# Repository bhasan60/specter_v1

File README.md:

## The Story Behind Specter V1
Welcome to the Specter V1! This is a custom 9-key macropad that I designed from the ground up. I wanted a dedicated board just for fun and maybe some custom shortcuts, but more importantly, I wanted to challenge myself to handle every single step of the hardware and software design process.

While I have a lot of experience with 3D modeling in Onshape, designing a custom 2-layer PCB from scratch in KiCad was a massive learning experience for me. It was fun though :)

## Hardware & Features
* **The Brain:** The whole board is powered by a Seeed Studio XIAO RP2040.
* **Inputs & Control:** It features 9 mechanical switches and a tactile rotary encoder.
* **Display:** I integrated a small OLED screen at the top to display certain GIFs or random stuff.
* **Custom PCB:** The board is a custom 2-layer design. To give it a personal touch, I added a custom New York Knicks logo to the front silkscreen to rep my city!
* **Enclosure:** The physical case is a custom two-part 3D-printed shell I modeled in Onshape. It is designed to fit snugly around the components and is secured together using M3 screws.
* **Firmware:** The macropad is fully programmable using QMK. 

## Screenshots
Overall Hackpad:

Schematic:

PCB:

Case:

I plan on fitting the two parts of the case together by threading the M3 screws into them.

## Bill of Materials (BOM)
* 1x Seeed Studio XIAO RP2040
* 9x Mechanical Switches
* 9x 1N4148 Diodes
* 1x Rotary Encoder (with push-button)
* 1x OLED Display
* 3D Printed Case (Top and Bottom)

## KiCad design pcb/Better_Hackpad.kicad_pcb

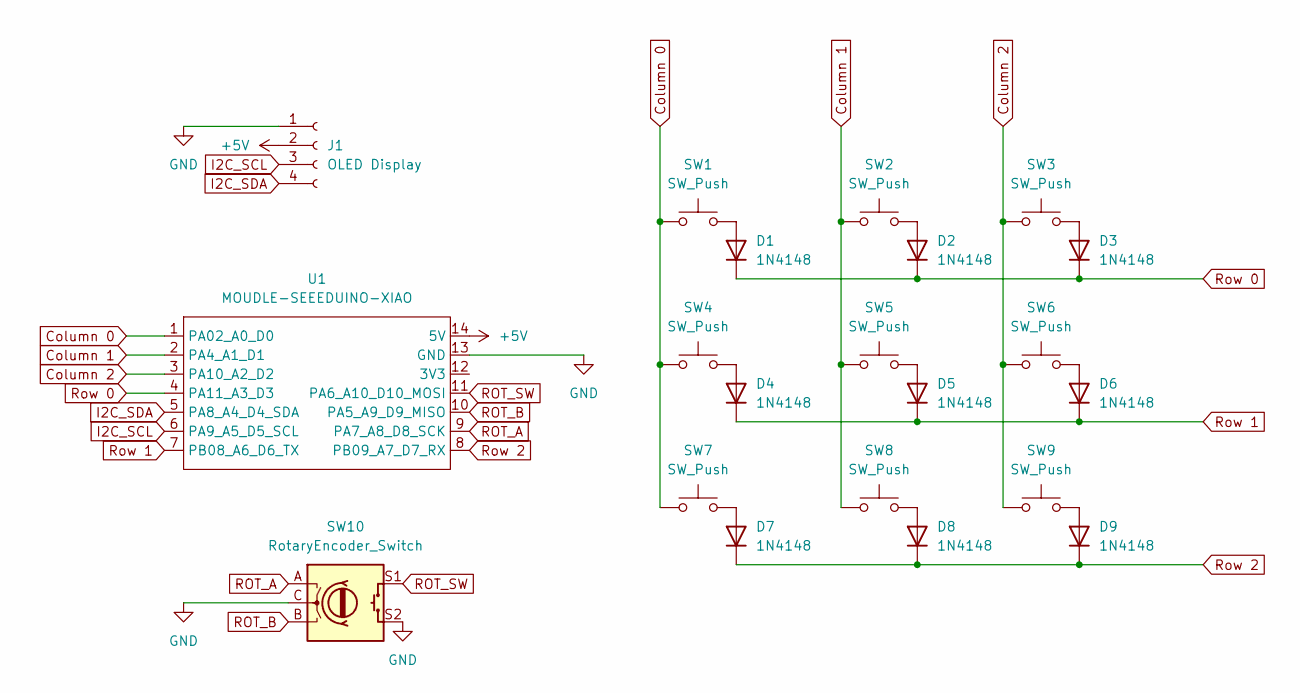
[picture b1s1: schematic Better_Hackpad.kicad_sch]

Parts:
D1, D2, D3, D4, D5, D6, D7, D8, D9: 1N4148; D_DO-35_SOD27_P7.62mm_Horizontal
J1: OLED Display; SSD1306-0.91-OLED-4pin-128x32
SW1, SW2, SW3, SW4, SW5, SW6, SW7, SW8, SW9: SW_Push; SW_Cherry_MX_1.00u_PCB
SW10: RotaryEncoder_Switch; RotaryEncoder_Alps_EC11E-Switch_Vertical_H20mm
U1: MOUDLE-SEEEDUINO-XIAO; XIAO-Generic-Hybrid-14P-2.54-21X17.8MM

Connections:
+5V: J1.2, U1.14 (5V)
Column 0: SW1.1, SW4.1, SW7.1, U1.1 (PA02_A0_D0)
Column 1: SW2.1, SW5.1, SW8.1, U1.2 (PA4_A1_D1)
Column 2: SW3.1, SW6.1, SW9.1, U1.3 (PA10_A2_D2)
GND: J1.1, SW10.C, SW10.S2, U1.13 (GND)
I2C_SCL: J1.3, U1.6 (PA9_A5_D5_SCL)
I2C_SDA: J1.4, U1.5 (PA8_A4_D4_SDA)
unnamed: D1.2 (A), SW1.2
unnamed: D2.2 (A), SW2.2
unnamed: D3.2 (A), SW3.2
unnamed: D4.2 (A), SW4.2
unnamed: D5.2 (A), SW5.2
unnamed: D6.2 (A), SW6.2
unnamed: D7.2 (A), SW7.2
unnamed: D8.2 (A), SW8.2
unnamed: D9.2 (A), SW9.2
ROT_A: SW10.A, U1.9 (PA7_A8_D8_SCK)
ROT_B: SW10.B, U1.10 (PA5_A9_D9_MISO)
ROT_SW: SW10.S1, U1.11 (PA6_A10_D10_MOSI)
Row 0: D1.1 (K), D2.1 (K), D3.1 (K), U1.4 (PA11_A3_D3)
Row 1: D4.1 (K), D5.1 (K), D6.1 (K), U1.7 (PB08_A6_D6_TX)
Row 2: D7.1 (K), D8.1 (K), D9.1 (K), U1.8 (PB09_A7_D7_RX)

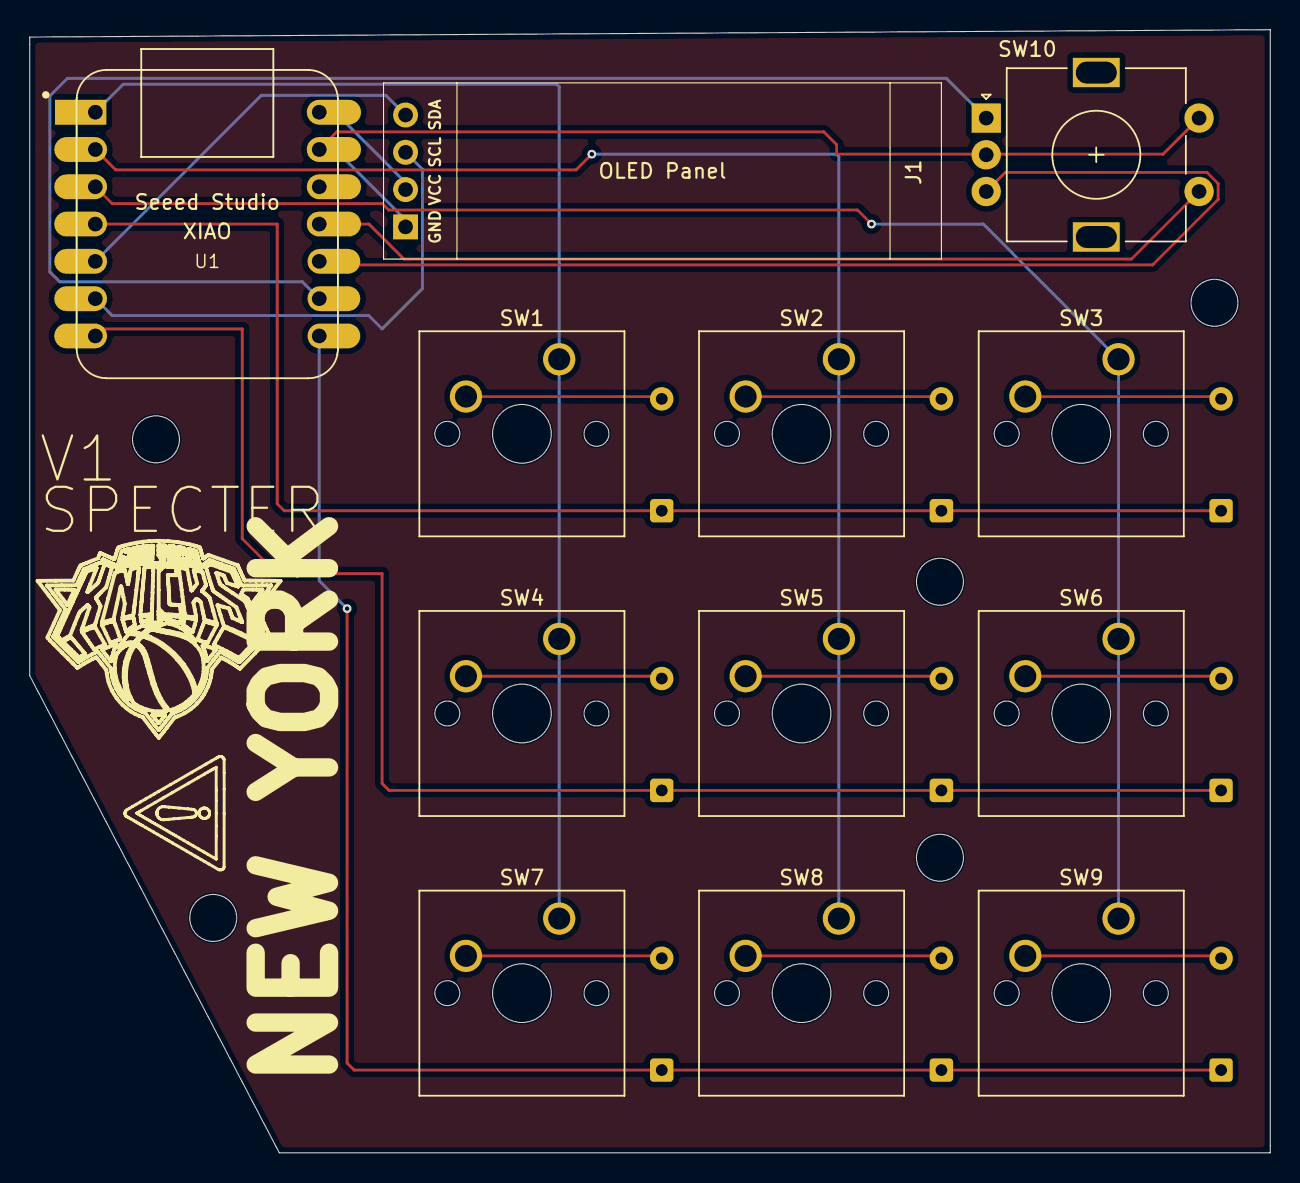
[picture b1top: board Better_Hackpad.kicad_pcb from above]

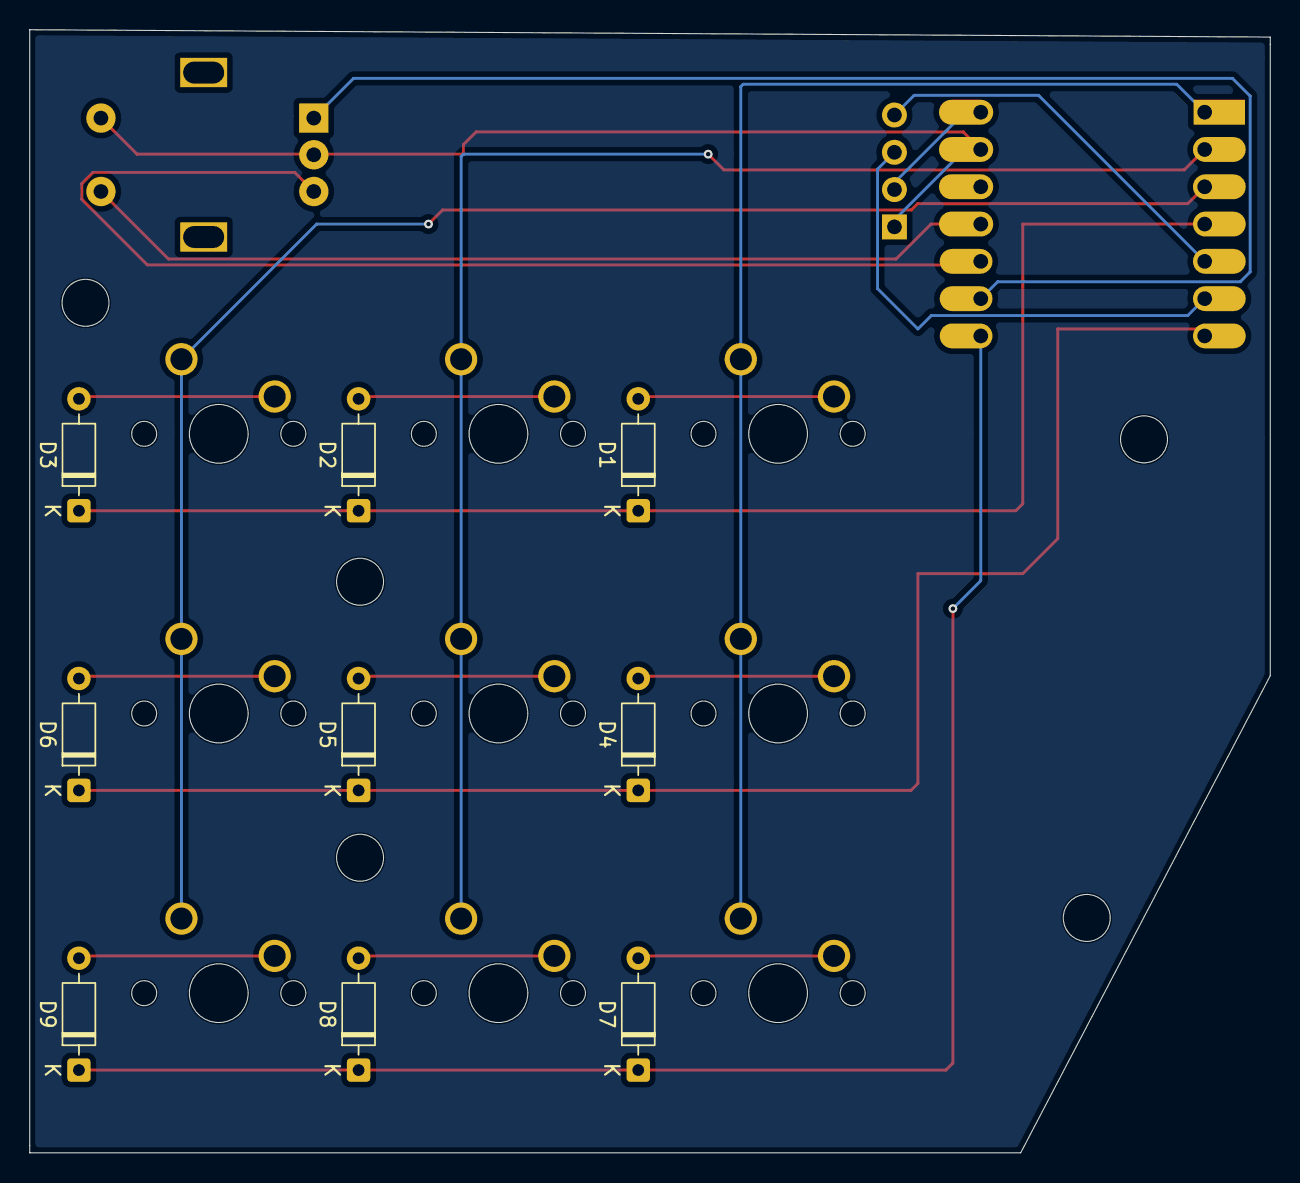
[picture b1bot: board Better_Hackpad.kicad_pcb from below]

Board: 2 copper layers, 84.5 x 76.5 mm, 21 parts (9 on the bottom side), 22 nets.

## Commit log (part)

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2026-06-22 Rename specter_v1.3mf to cad/specter_v1.3mf
2026-06-22 Update README with project details and BOM
    Added project description, screenshots, and BOM.
2026-06-22 Update README with images and case description
    Added images and descriptions for overall hackpad, schematic, PCB, and case.
2026-06-22 Replace schematic and PCB images in README
    Updated schematic and PCB images in README.
2026-06-22 Update README with images and BOM section
    Added images and information for overall hackpad, schematic, PCB, and case.
